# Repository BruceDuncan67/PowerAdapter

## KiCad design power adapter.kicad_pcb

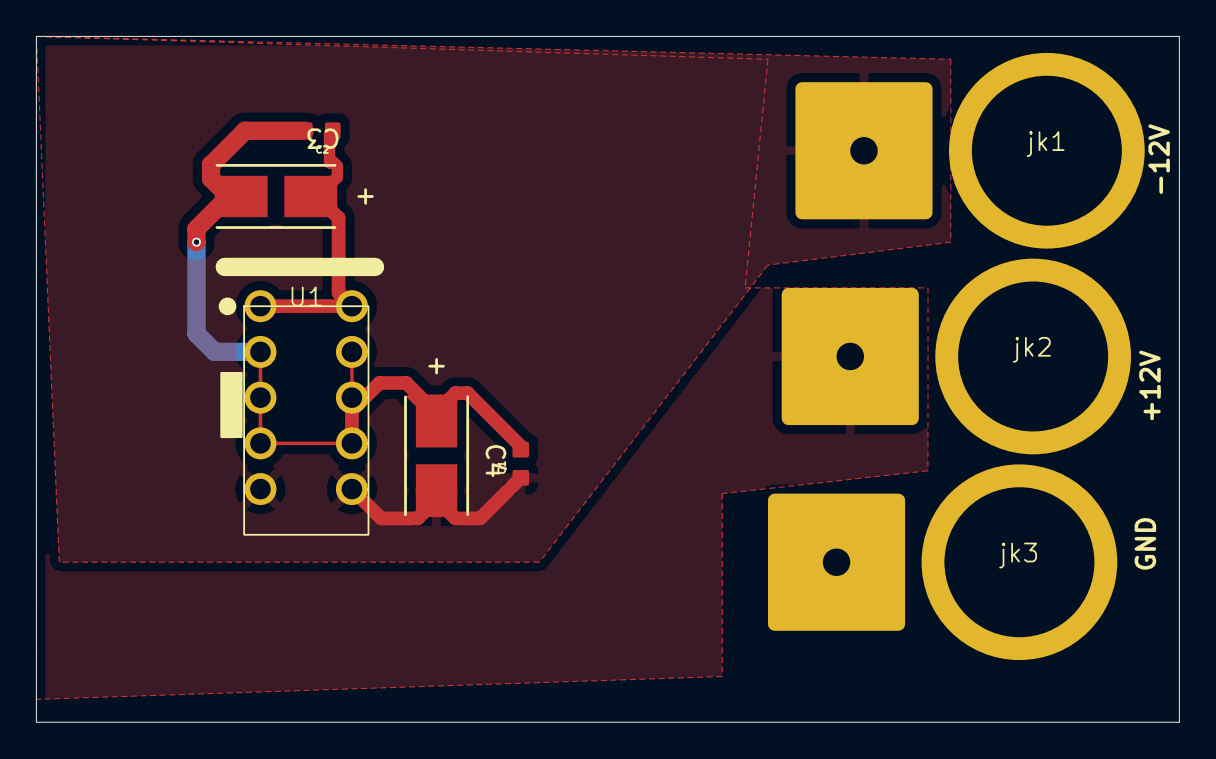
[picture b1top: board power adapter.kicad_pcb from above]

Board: 2 copper layers, 63.5 x 38.1 mm, 8 parts (0 on the bottom side), 4 nets.

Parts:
C1: .1uF; CAPC1608X90N
C2: .01uF; CAPC1608X90N
C3, C4: T491C106M025AT7280; 10uFtantcap
U1: Header2x5
jk1, jk2, jk3: Banana

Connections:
+12V: C2.1, C3.1, U1.1, U1.2, jk2.2
-12V: C1.1, C4.2, U1.9, U1.10, jk1.2
GND: C1.2, C2.2, C3.2, C4.1, U1.3, U1.5, U1.7, jk3.2
unnamed: U1.4, U1.6, U1.8

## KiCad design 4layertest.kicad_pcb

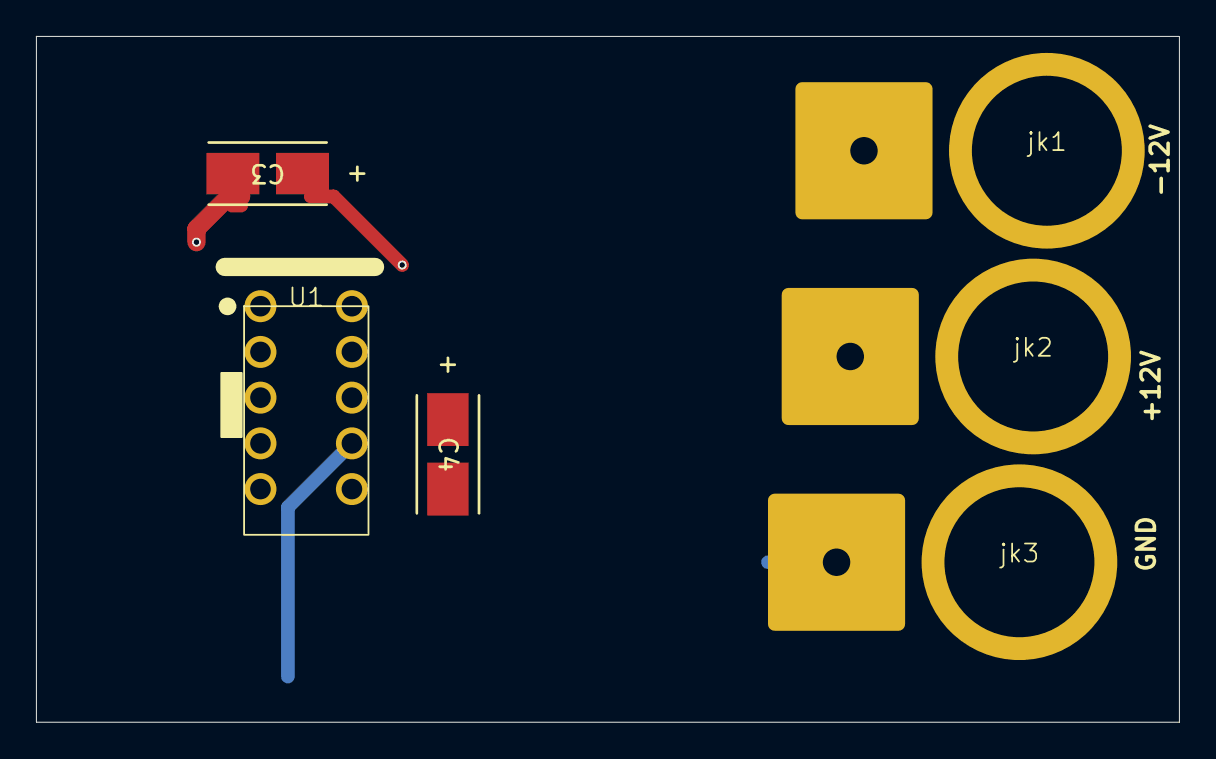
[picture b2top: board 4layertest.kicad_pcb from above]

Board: 4 copper layers, 63.5 x 38.1 mm, 6 parts (0 on the bottom side), 3 nets.

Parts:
C3, C4: T491C106M025AT7280; 10uFtantcap
U1: Header2x5
jk1, jk2, jk3: Banana

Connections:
+12V: C3.1, U1.1, U1.2, jk2.2
-12V: C4.2, U1.9, U1.10, jk1.2
GND: C3.2, C4.1, U1.3, U1.4, U1.5, U1.6, U1.7, U1.8, jk3.2

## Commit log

2025-10-06 test git
2025-10-06 additions
2025-10-06 added header footprint
2025-10-06 fixed header symbol
2025-10-07 header model added
    fppt print created by me and model added
2025-10-07 added esp32lib to project
2025-10-09 header adjusted
2025-10-09 board started
2025-10-09 customised the erc
2025-10-09 rotated power header
    rotated power header anotated schematic, turned on silkscreen layer
2025-10-09 added power lanes
2025-10-10 updateEuroHeader
2025-10-10 better power planes
    added better power planes and aded courtyards to a few footprints
2025-10-11 first commit of branch
2025-10-11 changed priority on power planes
2025-10-11 more wrk on power planes
2025-10-11 traces to cap
2025-10-12 added ceramic caps
2025-10-17 added mfp#for header
2025-10-18 fixedc2
2025-10-22 sertuppcbDRCvalues
2025-10-24 added comparitor section
2025-10-27 gold edge added
2025-10-27 added new board outline
    used an .svg file from corel to define board outlinr and resized the banana jack holes and scale for the model
2025-10-27 added graphics files to folder
2025-10-28 added dimensions
2025-11-03 more routing
2025-11-03 added default widths
2025-11-05 Mk2firstCommit
    more attention paid to fixing ERCs
